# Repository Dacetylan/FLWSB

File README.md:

# FLSWB

This GitHub repo contains all the source files for this project. 

## Documentation

The `docs/` folder contains all documentation in Markdown format, prepared for Docsify. This documentation can be found on the following page: https://dacetylan.github.io/FLWSB/#/

## Source code and boards

The `src/` folder contains all source files. This is all software written, modified or used and the KiCad projects of the developed PCBs.

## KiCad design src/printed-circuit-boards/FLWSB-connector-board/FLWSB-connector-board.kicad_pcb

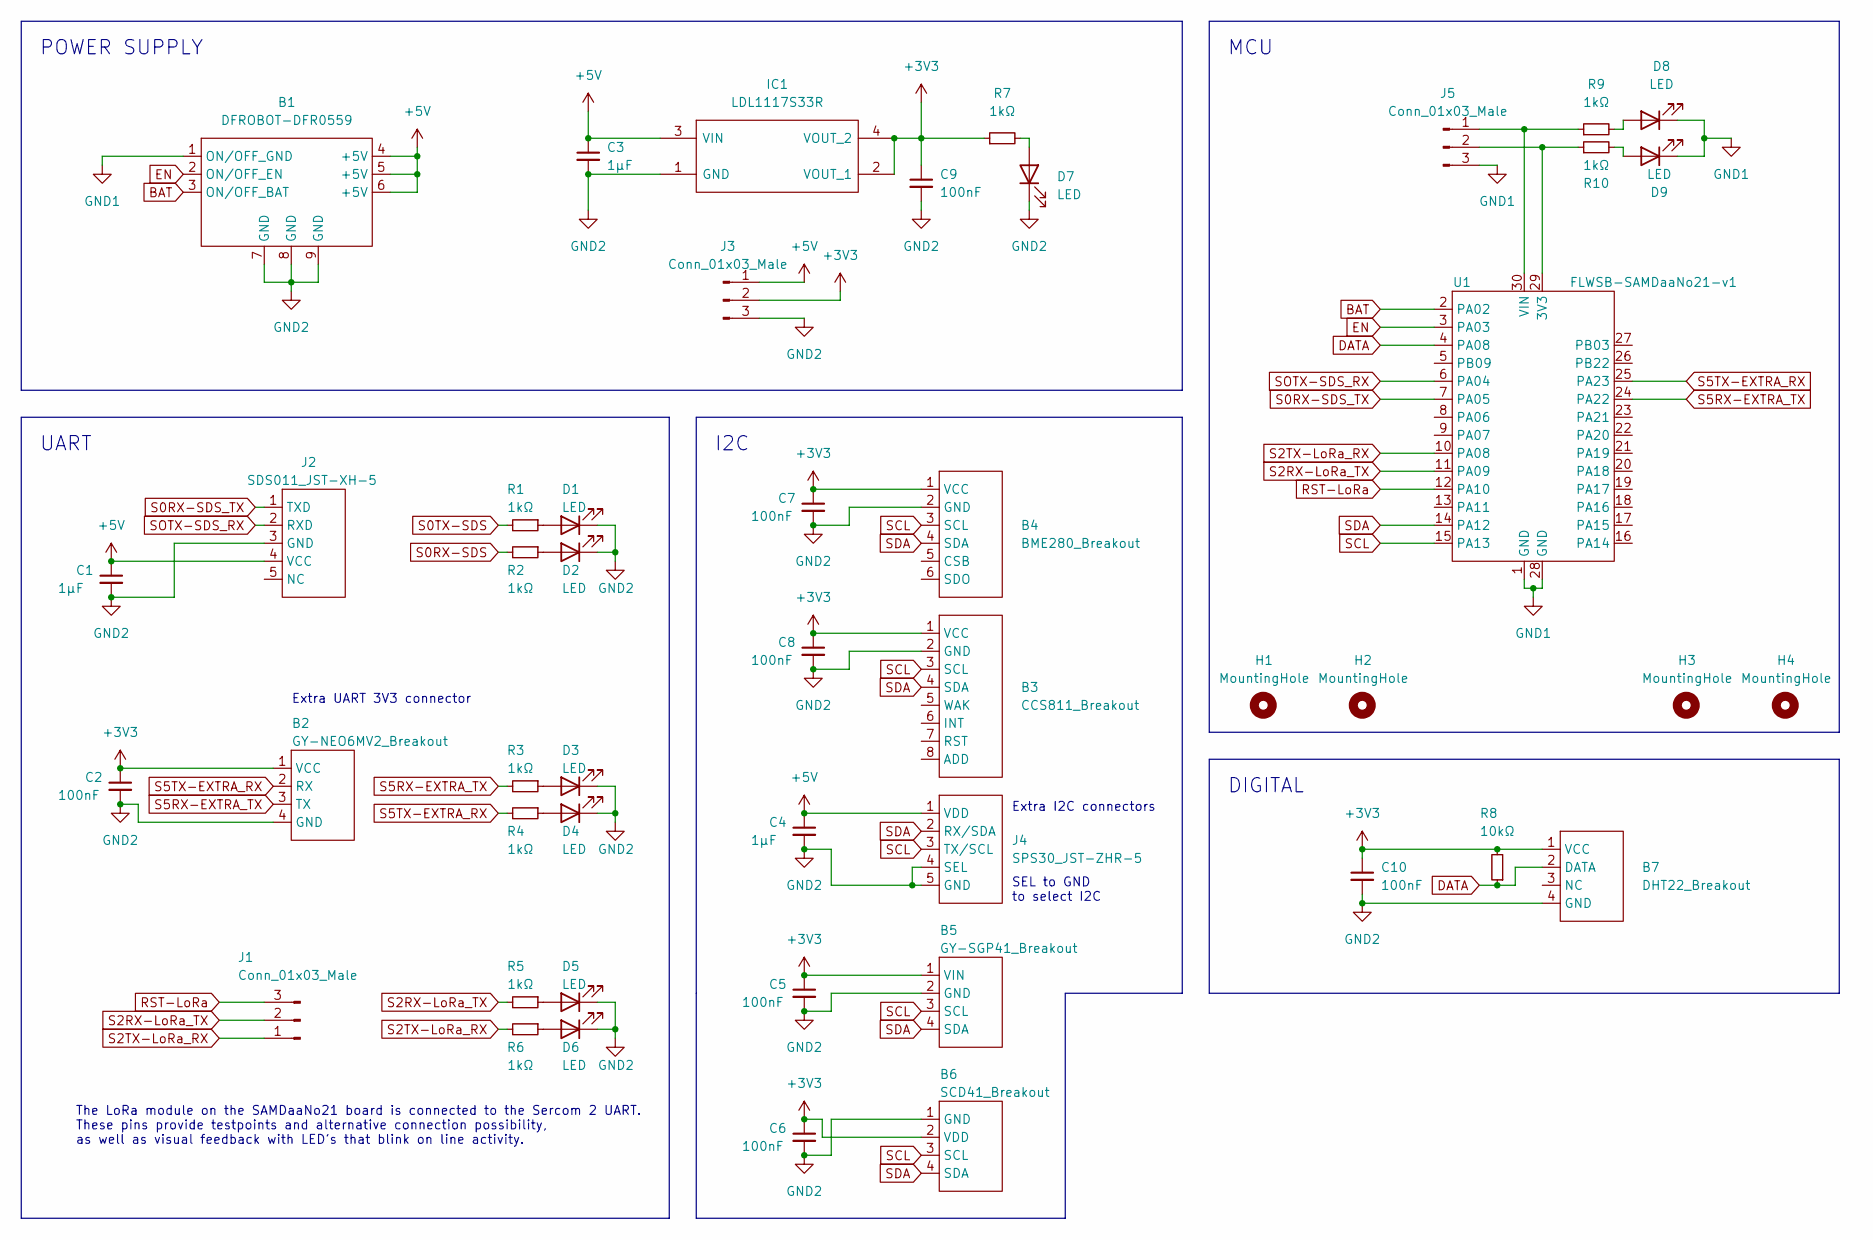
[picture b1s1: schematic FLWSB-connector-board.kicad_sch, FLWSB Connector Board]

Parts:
B1: DFROBOT-DFR0559
B2: GY-NEO6MV2_Breakout; PinHeader_1x04_P2.54mm_Vertical
B3: CCS811_Breakout
B4: BME280_Breakout; BM280_Breakout
B5: GY-SGP41_Breakout; PinHeader_1x04_P2.54mm_Vertical
B6: SCD41_Breakout; PinHeader_1x04_P2.54mm_Vertical
B7: DHT22_Breakout; PinHeader_1x04_P2.54mm_Vertical
C1, C3, C4: 1µF; C_0805_2012Metric_Pad1.18x1.45mm_HandSolder
C2, C5, C6, C7, C8, C9, C10: 100nF; C_0805_2012Metric_Pad1.18x1.45mm_HandSolder
D1, D2, D3, D4, D5, D6, D7, D8, D9: LED; LED_0805_2012Metric_Pad1.15x1.40mm_HandSolder
H1, H2, H3, H4: MountingHole; MountingHole_3.2mm_M3_Pad_Via
IC1: LDL1117S33R; SOT95P280X145-5N; Manufacturer_Part_Number LDL1117S33R; Mouser Part Number 511-LDL1117S33R
J1, J3, J5: Conn_01x03_Male; PinHeader_1x03_P2.54mm_Vertical
J2: SDS011_JST-XH-5; JST_XH_B5B-XH-A_1x05_P2.50mm_Vertical
J4: SPS30_JST-ZHR-5; JST_XH_B5B-XH-A_1x05_P2.50mm_Vertical
R1, R2, R3, R4, R5, R6, R7, R9, R10: 1kΩ; R_0805_2012Metric_Pad1.20x1.40mm_HandSolder
R8: 10kΩ; R_0805_2012Metric_Pad1.20x1.40mm_HandSolder
U1: FLWSB-SAMDaaNo21-v1

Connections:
+3V3: B2.1 (VCC), B3.1 (VCC), B4.1 (VCC), B5.1 (VIN), B6.2 (VDD), B7.1 (VCC), C2.1, C5.1, C6.1, C7.1, C8.1, C9.1, C10.1, IC1.2 (VOUT_1), IC1.4 (VOUT_2), J3.2, R7.1, R8.2
+5V: B1.4 (+5V), B1.5 (+5V), B1.6 (+5V), C1.1, C3.1, C4.1, IC1.3 (VIN), J2.4 (VCC), J3.1, J4.1 (VDD)
BAT: B1.3 (ON/OFF_BAT), U1.2 (PA02)
DATA: B7.2 (DATA), R8.1, U1.4 (PA08)
EN: B1.2 (ON/OFF_EN), U1.3 (PA03)
GND1: B1.1 (ON/OFF_GND), D8.1 (K), D9.1 (K), J5.3, U1.1 (GND), U1.28 (GND)
GND2: B1.7 (GND), B1.8 (GND), B1.9 (GND), B2.4 (GND), B3.2 (GND), B4.2 (GND), B5.2 (GND), B6.1 (GND), B7.4 (GND), C1.2, C2.2, C3.2, C4.2, C5.2, C6.2, C7.2, C8.2, C9.2, C10.2, D1.1 (K), D2.1 (K), D3.1 (K), D4.1 (K), D5.1 (K), D6.1 (K), D7.1 (K), IC1.1 (GND), J2.3 (GND), J3.3, J4.4 (SEL), J4.5 (GND)
unnamed: D1.2 (A), R1.1
unnamed: D2.2 (A), R2.1
unnamed: D3.2 (A), R3.1
unnamed: D4.2 (A), R4.1
unnamed: D5.2 (A), R5.1
unnamed: D6.2 (A), R6.1
unnamed: D7.2 (A), R7.2
unnamed: D8.2 (A), R9.2
unnamed: D9.2 (A), R10.2
unnamed: J5.1, R9.1, U1.30 (VIN)
unnamed: J5.2, R10.1, U1.29 (3V3)
RST-LoRa: J1.3, U1.12 (PA10)
S0RX-SDS: R2.2
S0RX-SDS_TX: J2.1 (TXD), U1.7 (PA05)
S0TX-SDS: R1.2
S2RX-LoRa_TX: J1.2, R5.2, U1.11 (PA09)
S2TX-LoRa_RX: J1.1, R6.2, U1.10 (PA08)
S5RX-EXTRA_TX: B2.3 (TX), R3.2, U1.24 (PA22)
S5TX-EXTRA_RX: B2.2 (RX), R4.2, U1.25 (PA23)
SCL: B3.3 (SCL), B4.3 (SCL), B5.3 (SCL), B6.3 (SCL), J4.3 (TX/SCL), U1.15 (PA13)
SDA: B3.4 (SDA), B4.4 (SDA), B5.4 (SDA), B6.4 (SDA), J4.2 (RX/SDA), U1.14 (PA12)
SOTX-SDS_RX: J2.2 (RXD), U1.6 (PA04)

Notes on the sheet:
SEL to GND to select I2C
MCU
DIGITAL
UART
POWER SUPPLY
Extra UART 3V3 connector
I2C
The LoRa module on the SAMDaaNo21 board is connected to the Sercom 2 UART. These pins provide testpoints and alternative connection possibility, as well as visual feedback with LED's that blink on line activity.
Extra I2C connectors

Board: 2 copper layers, 47 parts (0 on the bottom side), 27 nets, no tracks yet.

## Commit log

2022-09-30 started docsify docs
2022-09-30 Main Board Schema Documentatie
2022-10-02 Documentatie schema klaar
2022-10-02 Update documentatie schema
2022-10-03 Documentatie testpunten toegevoegd
2022-10-07 Update annotation in documentatie
2022-10-07 Update schema
2022-10-07 update documentatie pinout
2022-10-13 Documentatie sis
2022-10-16 Documentatie baavend + blokdiagram
2022-10-21 Update documentatie baavend
2022-10-28 SAMDaaNo21 pcb toegevoegd
2022-10-28 toevoegen SAMDaaNo21 PCB
2022-10-28 SAMDaaNo21 toegevoegd
2022-10-28 documentatie update
2022-10-28 Update documentatie data formatting
2022-10-28 update docs SAMDaaNo21
2022-10-28 Update documentatie data structuur
2022-10-30 added weerstation documentation + frontend documentation
2022-11-03 fixed docsify + added extra weather station documentation
2022-11-03 Eerste versie KiCad bibliotheek (symbool, footprint, 3d-model)
2022-11-04 documentatie SAMDaaNo21 KiCad lib
2022-11-04 afbeeldingen gefixt
2022-11-07 Update _sidebar.md
    Verbetering file paths
2022-11-07 Rename data-strcutuur.md to data-structuur.md
    Verbetering file naming
2022-11-15 SAMDaaNo21 bootloader bronnen toegevoegd
2022-11-15 aanpassingen bootloader voor SAMDaaNo21
2022-11-24 Backend update, new diagram, updated security, gitignore
2022-11-25 Default template files for security, TLS deactivated
2022-11-25 Backend update + Connector board documentatie met blokdiagram
2022-12-02 added .gitignore + added bare metal programming
2022-12-03 update uf2
2022-12-04 Backend on Linux + update weather station data + update connector board
2022-12-05 Begin documentatie Arduino IDE ondersteuning SAMDaaNo21
2022-12-09 Backend verplaatst naar src folder + update connector board, schema, pcb
2022-12-09 Correctie documentatie plaatsing
2022-12-11 SAMDaaNo21 Arduino IDE ondersteuning documentatie
2022-12-11 Uitleg over repo toegevoegd
2022-12-11 pinout, ArduinoCore-samd en BOSSA toegevoegd als submodule
2022-12-11 docs: toevoeging syntax highlighting en GitHub link
2022-12-16 Update data structuur + backend troubleshooting + update connector board
2022-12-17 Update on documentation consistency + intro weather station
2022-12-17 Onderzoek behuizing met zonnepanelen
2022-12-18 Update backend, security, solar power
2022-12-18 Verbeteringen
2022-12-19 Verplaatsen arduino-core documentatie
2022-12-20 update submodule repos
2022-12-20 repo introductie naar engel
2022-12-23 Update Doc Data Formatting + Mosquitto logging + Grafana visualisatie
2022-12-23 Indroductietekst
2022-12-26 docs aangevuld
2022-12-26 Update data formatting + update backend diagram + foto's demo opstelling
2022-12-26 Update data formatting
2023-01-16 Updated docs structure + added Flexibility and Boards Design + Updates
2023-01-17 Update documentatie: demo, backend, data-formatting, enclosure, intro
2023-01-17 Toevoeging content SAMDaaNo21
2023-01-18 Aanpassingen embedded programming, toevoegingen docsify
2023-01-18 blokdiagram aangepast
2023-01-18 Weather station documentation
2023-01-18 submodules up-to-date
2023-01-18 documentatie SAMDaaNo21
2023-01-18 Data Formatting Update
2023-01-19 Backup node-red flows + current deployment + update docs sis + real-data
2023-01-19 Update backend documentatie: baavend + node-red
2023-01-19 Update documentatie: backend volledig
2023-01-19 Update documentatie frontend
2023-01-19 Update future improvements
2023-01-19 Update sidebar
2023-01-19 toekomstige toevoegingen SAMDaaNo21
2023-01-19 documentatie weather station, misschien dat het nu wel allemaal erbij zit???? Vorige keer was een stuk gewoon verdwenengit add .
2023-01-19 SIS implementatie ArduinoCore
2023-01-19 Update documentatie backend + sidebar + future improvements
2023-01-20 Update docs BaaVend + backup files
2023-01-23 Added exam presentation to docs
